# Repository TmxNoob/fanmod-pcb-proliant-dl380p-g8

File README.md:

### Made in KiCad

I provide only KiCad files because different PCB fabs require different export methods
Just google "[your preffered pcb fab] KiCad guide"

This mod is tested and needs some hacking around to work properly.
For example some of dl380p g8 fan revisions have thinner ears on the connectors so for those you need to have thinner pcbs (6mm ones from jlcpcb work).
To have the connector that goes into the motherboard make proper contact 80% of the time instead of 30% you need to solder it on at an angle (will add pics soon).
More info about the fanmod here:
https://github.com/TmxNoob/proliant-fan-mod

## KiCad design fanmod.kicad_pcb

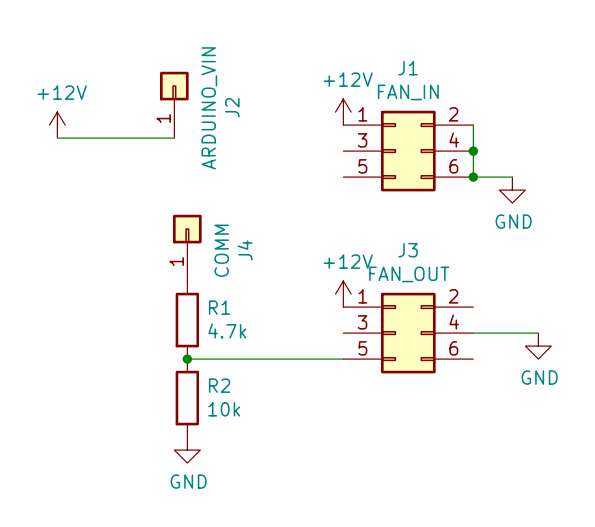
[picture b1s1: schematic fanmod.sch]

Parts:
J1: FAN_IN; PinSocket_2x03_P2.00mm_Vertical
J2: ARDUINO_VIN; PinHeader_1x01_P2.00mm_Vertical
J3: FAN_OUT; PinHeader_2x03_P2.00mm_Horizontal
J4: COMM; PinHeader_1x01_P2.00mm_Vertical
R1: 4.7k; R_0603_1608Metric_Pad1.05x0.95mm_HandSolder
R2: 10k; R_0603_1608Metric_Pad1.05x0.95mm_HandSolder

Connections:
+12V: J1.1, J2.1, J3.1
GND: J1.2, J1.4, J1.6, J3.4, R2.2
unnamed: J3.5, R1.2, R2.1
unnamed: J4.1, R1.1

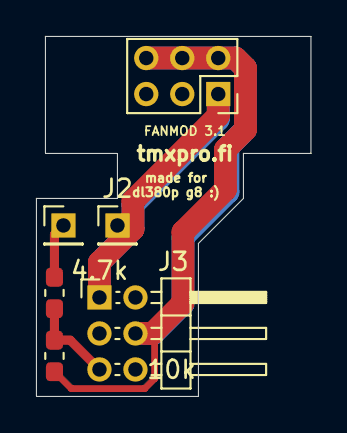
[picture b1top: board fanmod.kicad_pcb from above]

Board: 2 copper layers, 15.2 x 20.0 mm, 6 parts (0 on the bottom side), 4 nets.

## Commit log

2020-10-16 Fix README.md
2020-10-18 Edit README
2021-01-31 Update README.md
    Add some details to readme.
